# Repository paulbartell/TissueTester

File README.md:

TissueTester
============

TissueTester

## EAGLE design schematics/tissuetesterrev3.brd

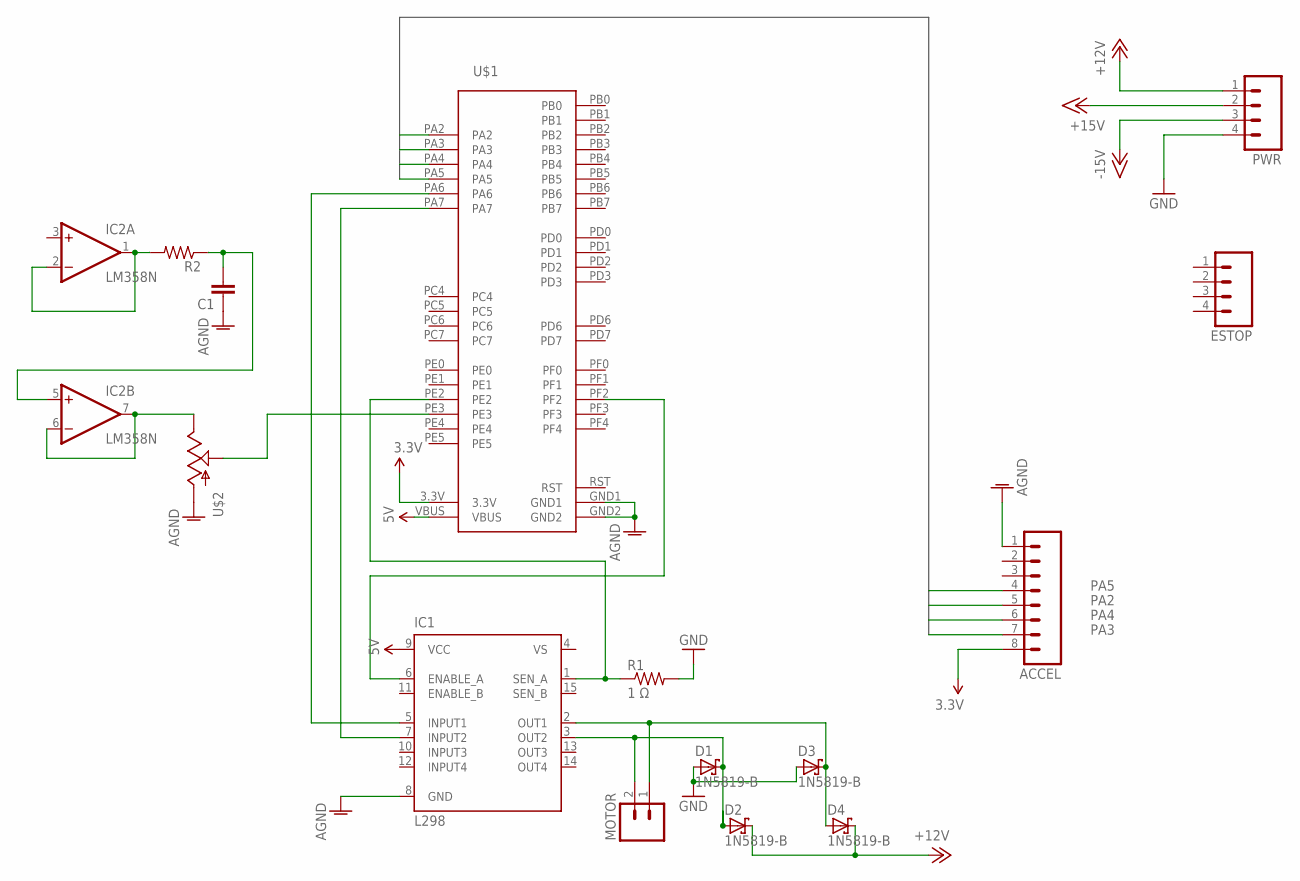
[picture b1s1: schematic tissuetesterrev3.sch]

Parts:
ACCEL: M08LOCK; 1X08_LOCK
C1: CAPKIT; CAP-PTH-SMALL-KIT
D1, D2, D3, D4: 1N5819-B; DO41-7.6
ESTOP: M04LOCK; 1X04_LOCK
IC1: L298; MULTIWATT-15
IC2: LM358N; DIL08
MOTOR: M023.5MM; SCREWTERMINAL-3.5MM-2
PWR: M04SCREW; SCREWTERMINAL-3.5MM-4
R1: 1 Ω; AXIAL-0.6
R2: RESISTORKIT; AXIAL-0.3-KIT
U$1: STELLARIS-LAUNCHPADSTELLARIS-LAUNCHPAD; LAUNCHPAD-XL
U$2: POT; ALPS_POT

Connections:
3.3V: ACCEL.8, U$1.3.3V
5V: IC1.9 (VCC), U$1.VBUS
+12V: D2.C, D4.C, PWR.1
+15V: PWR.2
-15V: PWR.3
AGND: ACCEL.1, C1.1, IC1.8 (GND), U$1.GND1, U$1.GND2, U$2.P$3 (A)
GND: D1.A, D3.A, PWR.4, R1.P$2 (2)
unnamed: IC1.6 (ENABLE_A), U$1.PF2
unnamed: IC1.5 (INPUT1), U$1.PA6
unnamed: IC1.7 (INPUT2), U$1.PA7
unnamed: IC1.1 (SEN_A), R1.P$1 (1), U$1.PE2
unnamed: IC2.6 (-IN), IC2.7 (OUT), U$2.P$1 (E)
unnamed: D3.C, D4.A, IC1.2 (OUT1), MOTOR.1
unnamed: D1.C, D2.A, IC1.3 (OUT2), MOTOR.2
unnamed: IC2.1 (OUT), IC2.2 (-IN), R2.P$2 (2)
unnamed: C1.2, IC2.5 (+IN), R2.P$1 (1)
unnamed: U$1.PE3, U$2.P$2 (S)
PA2: ACCEL.5, U$1.PA2
PA3: ACCEL.7, U$1.PA3
PA4: ACCEL.6, U$1.PA4
PA5: ACCEL.4, U$1.PA5
RST: U$1.RST
V+: IC2.8 (V+)
V-: IC2.4 (V-)
VS: IC1.4 (VS)

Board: 2 copper layers, 15 parts (0 on the bottom side), 19 nets, no tracks yet.

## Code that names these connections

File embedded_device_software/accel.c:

/*
 * accel.c
 *
 *  Created on: May 15, 2013
 *      Author: Paul Bartell
 *      Connects to an accelerometer and fetches data at 1kHz, storing in a global variable.
 */

#include "inc/hw_memmap.h"
#include "inc/hw_ssi.h"
#include "inc/hw_types.h"
#include "driverlib/ssi.h"
#include "driverlib/gpio.h"
#include "driverlib/sysctl.h"
#include "utils/uartstdio.h"
#include "accel.h"
#include "driverlib/pin_map.h"
#include "driverlib/rom_map.h"

#define NUM_SSI_DATA 2
#define CTRL_REG1 0x20 //0b00111111
#define CTRL_REG4 0x23 //0b00110000
#define XL 0x28
#define XH 0x29
#define YL 0x2a
#define YH 0x2b
#define ZL 0x2c
#define ZH 0x2d
#define WRITE 0x80
#define READ 0x00
#define INCREMENT 0x40

signed long accel;
unsigned long ulDataRx[2];

void accelInit(void){

    //
    // Enable Peripheral Clocks
    //
    MAP_SysCtlPeripheralEnable(SYSCTL_PERIPH_SSI0);
    MAP_SysCtlPeripheralEnable(SYSCTL_PERIPH_GPIOA);

    //
    // Enable port PA4 for SSI0 SSI0RX
    //
    MAP_GPIOPinConfigure(GPIO_PA4_SSI0RX);
    MAP_GPIOPinTypeSSI(GPIO_PORTA_BASE, GPIO_PIN_4);

    //
    // Enable port PA2 for SSI0 SSI0CLK
    //
    MAP_GPIOPinConfigure(GPIO_PA2_SSI0CLK);
    MAP_GPIOPinTypeSSI(GPIO_PORTA_BASE, GPIO_PIN_2);

    //
    // Enable port PA3 for SSI0 SSI0FSS
    //
    MAP_GPIOPinConfigure(GPIO_PA3_SSI0FSS);
    MAP_GPIOPinTypeSSI(GPIO_PORTA_BASE, GPIO_PIN_3);

    //
    // Enable port PA5 for SSI0 SSI0TX
    //
    MAP_GPIOPinConfigure(GPIO_PA5_SSI0TX);
    MAP_GPIOPinTypeSSI(GPIO_PORTA_BASE, GPIO_PIN_5);


	// Assume SSI initialization is taken care of in the pins file.
	SSIConfigSetExpClk(SSI0_BASE, SysCtlClockGet(), SSI_FRF_MOTO_MODE_0,
	                       SSI_MODE_MASTER, 10000000, 8); // Set clock 10MHz and frame length (8 bits)
	SSIEnable(SSI0_BASE);
	// Initialize accelerometer module on SSI0 using SPI interface

    while(SSIDataGetNonBlocking(SSI0_BASE, &ulDataRx[0]))
    {
    }

    // Setup Accelerometer

    SSIDataPut(SSI0_BASE, (WRITE | CTRL_REG4));
    SSIDataPut(SSI0_BASE, 0x30);
    SSIDataPut(SSI0_BASE, (WRITE | CTRL_REG1));
    SSIDataPut(SSI0_BASE, 0x3F);
    //Enable with 1kHz data rate
}

void accelInt(void){
	SSIDataPut(SSI0_BASE, READ | XL | INCREMENT);
	SSIDataGet(SSI0_BASE, &ulDataRx[0]);
	SSIDataGet(SSI0_BASE, &ulDataRx[1]);

	accel = (ulDataRx[0] << 8 )| (ulDataRx[1]);

}

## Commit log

2013-03-02 created structs.h
    Packet structs for communication between stellaris board and PC host.
2013-03-02 Project files
    Added project files and some main files.. started pwm implementation.
2013-03-27 Added barebones ADC code
2013-04-01 Preliminary Update
    I've figured out how to do interrupt driven ADC and it's sort of what I
    have going right now, but I need to make some changes. I'm committing
    what I have now in case we need to revert.
2013-04-02 ADC Works
    As of now, we're only sampling with one ADC, the one for current. We can
    add the LVDT measurements using the second ADC very easily.
2013-04-02 added uart stuff
2013-04-02 Code cleanup.. Made it compile under GCC on osx
2013-04-02 Cleanup
2013-04-02 more cleanup
2013-04-02 Non-working / non-compiling..
    Committed so Yan can see it.
2013-04-03 Fixed some minor issues
    Working on adding the second ADC into the code, losing my mind here.
2013-04-03 ADC is done
    ADC works for LVDT and current measurements, time to celebrate.
2013-04-03 Formatting stuff
2013-04-03 Minor updates
2013-04-03 Combined main.c is finished
    Consolidated the PWM and ADC functions and they both work.
2013-04-03 Cleaned up trash files
2013-04-03 blah
2013-04-03 newpins.c working version
2013-04-03 It works!
2013-04-06 Nice and pretty version
2013-04-08 Started work on the PID
2013-04-17 Required commit
2013-04-19 PID Progress
2013-04-19 Fixed Horrible Errors
    I hate github
2013-04-25 More progress on PID
2013-04-25 PD controller done
    Just need to implement the interrupt
2013-05-03 Made Shit work.
2013-05-05 Proportional control working... high steady state error.
2013-05-05 Integral term is now fully implemented; needs testing.
2013-05-05 Almost have it working, need to iron out some bugs
2013-05-05 not quite working.
2013-05-06 more work
2013-05-06 Anti-windup works now
2013-05-06 The code works, except that I need to change the parsing around a bit.
2013-05-06 Added limts for max control effort..
    start i at 560 rather than 0.. okay response, but some oscillation.
2013-05-10 still not working.,
2013-05-16 Working on trajectory generation
2013-05-21 Implemented start/stop functionality
2013-05-21 Don't know what this commit is for
2013-05-22 SSI commit
2013-05-22 lakdhglkasndlgkads
2013-05-22 Consolidated the interface with what we have
    It won't compile because TI is dumb.
2013-05-22 Compiles but doesn't work.
    It works on my computer, but that's because I don't have the PID stuff
    in the same file. Looks like we have a bunch of debugging to do....
2013-05-22 Probably fixed it.
2013-05-22 Using Stellaris sine library.
2013-05-22 testing
2013-05-23 now it works with a trajectory.. need to tune KPID...
2013-05-23 random commit
2013-05-23 Set frequency command now works.
2013-05-25 Set frequency works.. a bit more stable.. but still seems to have random crashes.
2013-05-28 PID generalized
2013-05-29 First USB commit
2013-05-29 Started work on trajectory generation
2013-05-30 More progress on trajectory
2013-05-30 Progress
2013-06-01 DAT PROGRESSSSSSSS
2013-06-02 Estop works, Current controller works.
2013-06-04 Stuff kind of works. Oh, and yeah, PROGRESS.
2013-06-04 Working software.. Committing
2013-06-04 Committing to Final Branch
2013-06-04 Fixed readme file
2013-06-04 First commit of schematic/board files

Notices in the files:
parts and their libraries:
SparkFun-Connectors: Licensing: CC v3.0 Share-Alike You are welcome to use this library for commercial purposes.
